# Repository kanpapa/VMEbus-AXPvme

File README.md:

# VMEbus-AXPvme
This repository contains documentation and sources for running DEC AXPvme 230

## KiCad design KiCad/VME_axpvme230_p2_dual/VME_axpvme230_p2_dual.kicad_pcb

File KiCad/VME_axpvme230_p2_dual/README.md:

# VME_axpvme230_p2_dual

DEC AXPvme 230 moduleをVMEラックに実装するためのAXPvme Dual Slot Breakout moduleです。

## Breakout boardの設計方針

* VMEラックにおいてAXPvme 230 moduleに確実に電源を供給することを目標にします。
* SCSIやその他の信号についてはコネクタに引き出すだけにします。
* 電源ラインは4層基板にすることで他の信号から電源ラインを分離します。

## KiCadデータ

KiCADで設計からガーバーデータの作成を行いました。

* [回路図](./VME_axpvme230_p2_dual_sch.pdf)
* [BOM](./VME_axpvme230_p2_dual.csv)
* [Garber](./gerber/)

## Dual Slot Breakout boardのイメージ図

## Disclaimer
The contents of this repository are the result of personal research and are provided "as is" without any warranty.

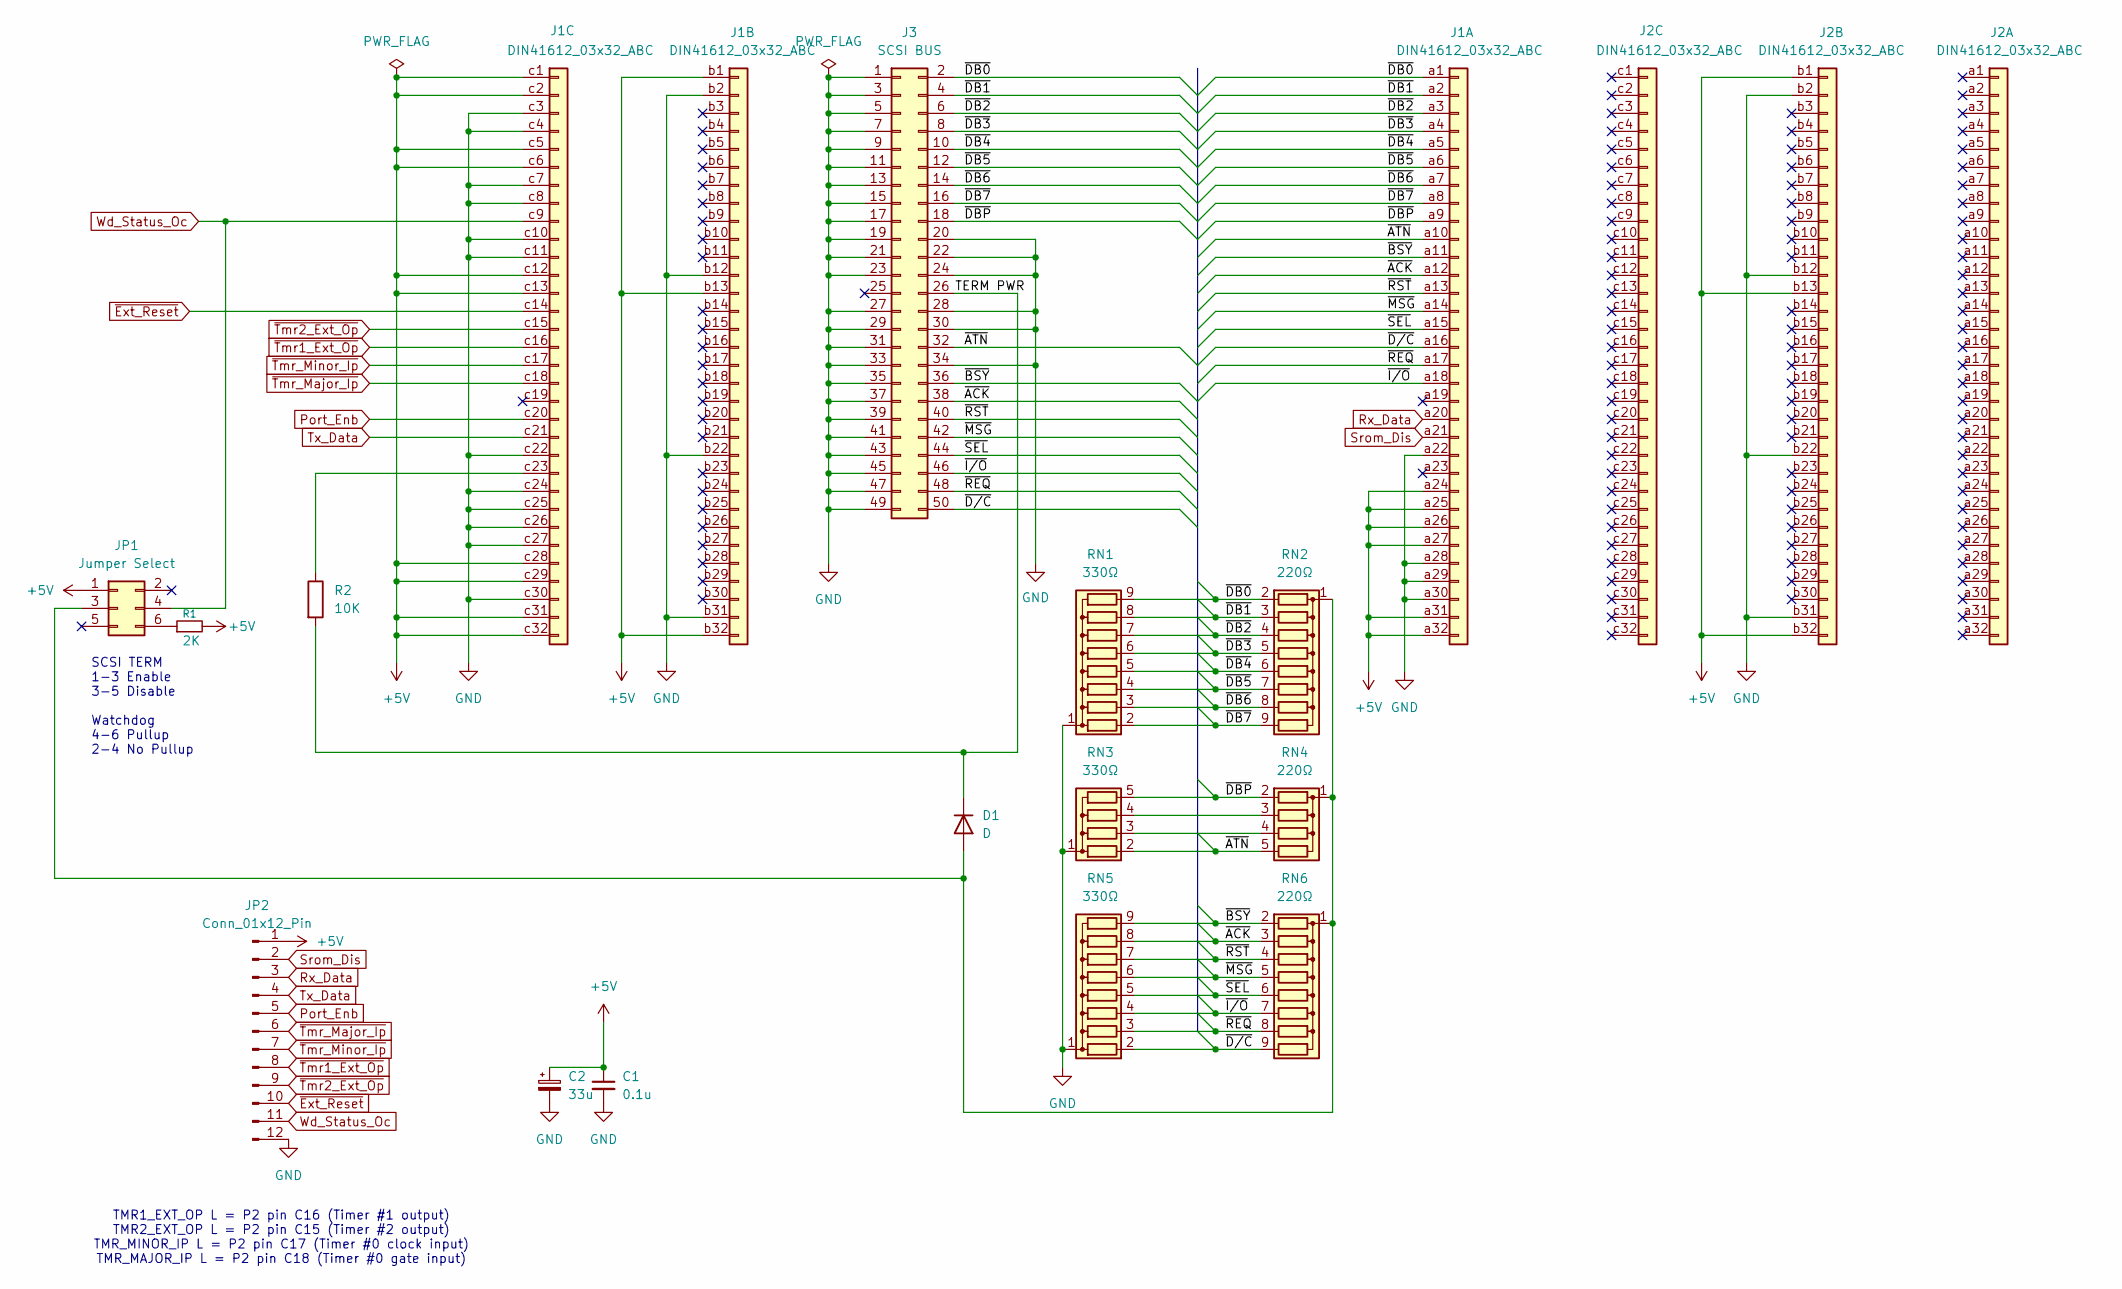
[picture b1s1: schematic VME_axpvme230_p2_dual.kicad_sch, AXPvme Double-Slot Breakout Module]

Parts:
C1: 0.1u; C_Disc_D3.4mm_W2.1mm_P2.50mm
C2: 33u; C_Radial_D4.0mm_H5.0mm_P1.50mm
D1: D; D_A-405_P7.62mm_Horizontal
J1, J2: DIN41612_03x32_ABC; DIN41612_C_3x32_Female_Vertical_THT
J3: SCSI BUS; IDC-Header_2x25_P2.54mm_Vertical
JP1: Jumper Select; PinHeader_2x03_P2.54mm_Vertical
JP2: Conn_01x12_Pin; PinHeader_1x12_P2.54mm_Vertical
R1: 2K; R_Axial_DIN0207_L6.3mm_D2.5mm_P7.62mm_Horizontal
R2: 10K; R_Axial_DIN0207_L6.3mm_D2.5mm_P7.62mm_Horizontal
RN1, RN5: 330Ω; R_Array_SIP9
RN2, RN6: 220Ω; R_Array_SIP9
RN3: 330Ω; R_Array_SIP5
RN4: 220Ω; R_Array_SIP5

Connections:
+5V: C1.1, C2.1, J1.a24, J1.a25, J1.a26, J1.a27, J1.a31, J1.a32, J1.b1, J1.b13, J1.b32, J1.c1, J1.c2, J1.c5, J1.c6, J1.c12, J1.c13, J1.c28, J1.c29, J1.c31, J1.c32, J2.b1, J2.b13, J2.b32, JP1.1, JP2.1, R1.2
/TERM PWR: D1.1 (K), J3.26, R2.2
/~ACK: J1.a12, J3.38, RN5.8 (R7), RN6.3 (R2)
/~ATN: J1.a10, J3.32, RN3.2 (R1), RN4.5 (R4)
/~BSY: J1.a11, J3.36, RN5.9 (R8), RN6.2 (R1)
/~DB0: J1.a1, J3.2, RN1.9 (R8), RN2.2 (R1)
/~DB1: J1.a2, J3.4, RN1.8 (R7), RN2.3 (R2)
/~DB2: J1.a3, J3.6, RN1.7 (R6), RN2.4 (R3)
/~DB3: J1.a4, J3.8, RN1.6 (R5), RN2.5 (R4)
/~DB4: J1.a5, J3.10, RN1.5 (R4), RN2.6 (R5)
/~DB5: J1.a6, J3.12, RN1.4 (R3), RN2.7 (R6)
/~DB6: J1.a7, J3.14, RN1.3 (R2), RN2.8 (R7)
/~DB7: J1.a8, J3.16, RN1.2 (R1), RN2.9 (R8)
/~DBP: J1.a9, J3.18, RN3.5 (R4), RN4.2 (R1)
/~D/C: J1.a16, J3.50, RN5.2 (R1), RN6.9 (R8)
/~I/O: J1.a18, J3.46, RN5.4 (R3), RN6.7 (R6)
/~MSG: J1.a14, J3.42, RN5.6 (R5), RN6.5 (R4)
/~REQ: J1.a17, J3.48, RN5.3 (R2), RN6.8 (R7)
/~RST: J1.a13, J3.40, RN5.7 (R6), RN6.4 (R3)
/~SEL: J1.a15, J3.44, RN5.5 (R4), RN6.6 (R5)
GND: C1.2, C2.2, J1.a22, J1.a28, J1.a29, J1.a30, J1.b2, J1.b12, J1.b22, J1.b31, J1.c3, J1.c4, J1.c7, J1.c8, J1.c10, J1.c11, J1.c22, J1.c24, J1.c25, J1.c26, J1.c27, J1.c30, J2.b2, J2.b12, J2.b22, J2.b31, J3.1, J3.3, J3.5, J3.7, J3.9, J3.11, J3.13, J3.15, J3.17, J3.19, J3.20, J3.21, J3.22, J3.23, J3.24, J3.27, J3.28, J3.29, J3.30, J3.31, J3.33, J3.34, J3.35, J3.37, J3.39, J3.41, J3.43, J3.45, J3.47, J3.49, JP2.12, RN1.1 (common), RN3.1 (common), RN5.1 (common)
unnamed: D1.2 (A), JP1.3, RN2.1 (common), RN4.1 (common), RN6.1 (common)
unnamed: J1.c23, R2.1
unnamed: JP1.6, R1.1
unnamed: RN3.3 (R2), RN4.4 (R3)
unnamed: RN3.4 (R3), RN4.3 (R2)
Port_Enb: J1.c20, JP2.5
Rx_Data: J1.a20, JP2.3
Srom_Dis: J1.a21, JP2.2
Tx_Data: J1.c21, JP2.4
Wd_Status_Oc: J1.c9, JP1.4, JP2.11
~Ext_Reset: J1.c14, JP2.10
~Tmr1_Ext_Op: J1.c16, JP2.8
~Tmr2_Ext_Op: J1.c15, JP2.9
~Tmr_Major_Ip: J1.c18, JP2.6
~Tmr_Minor_Ip: J1.c17, JP2.7

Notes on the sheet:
TMR1_EXT_OP L = P2 pin C16 (Timer #1 output) TMR2_EXT_OP L = P2 pin C15 (Timer #2 output) TMR_MINOR_IP L = P2 pin C17 (Timer #0 clock input) TMR_MAJOR_IP L = P2 pin C18 (Timer #0 gate input)
SCSI TERM 1-3 Enable 3-5 Disable Watchdog 4-6 Pullup 2-4 No Pullup

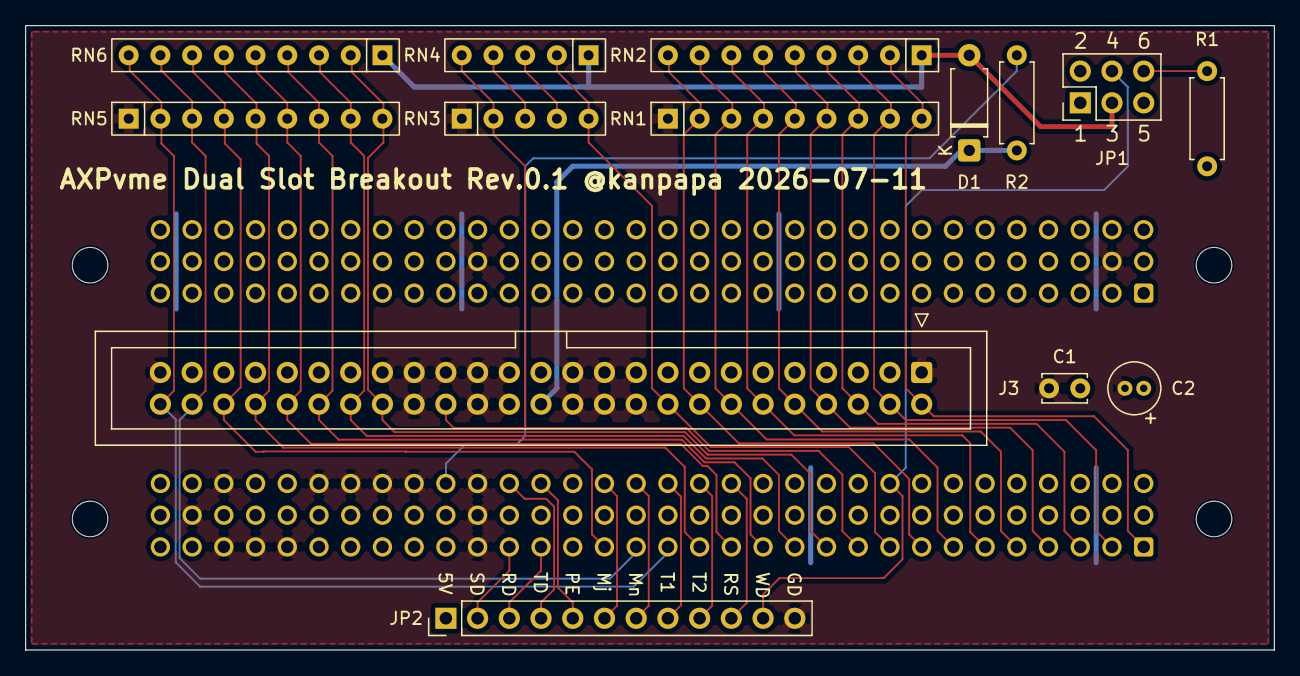
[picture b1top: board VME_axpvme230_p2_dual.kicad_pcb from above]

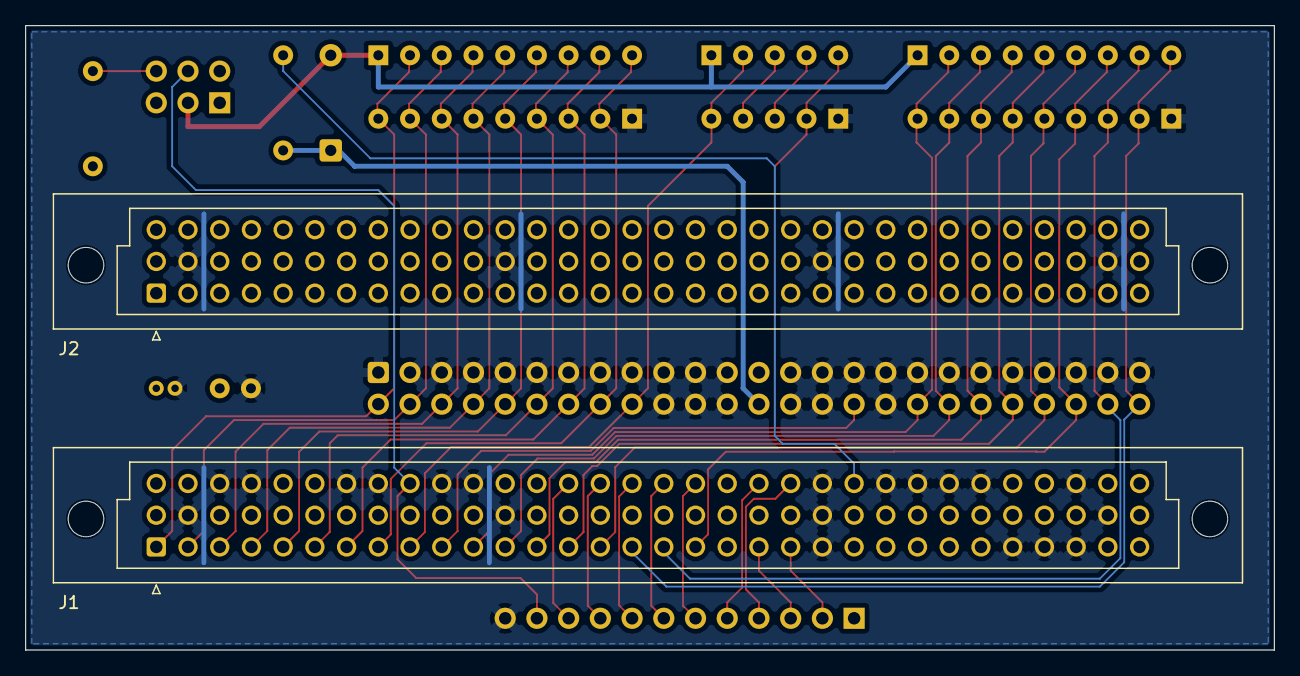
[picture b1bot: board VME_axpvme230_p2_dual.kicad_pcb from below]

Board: 4 copper layers, 100.0 x 50.0 mm, 16 parts (2 on the bottom side), 36 nets.

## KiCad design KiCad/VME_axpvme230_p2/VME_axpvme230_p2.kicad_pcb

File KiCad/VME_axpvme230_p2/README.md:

# VMEbus-axpvme230_p2

AXPvme 230 moduleを動作させるためには専用のAXPvme Breakout module (54-22621-01)が必要です。  
ドキュメントを参考にして簡易的なAXPvme Breakout boardを製作します。

## Breakout boardの設計方針

* AXPvme 230 moduleに確実に電源を供給することを目標にします。
* 試作の段階なので、VMEラックへの取り付けは行わず机上で確認できるようにシンプルなものにします。
* SCSIやその他の信号についてはコネクタに引き出すだけにします。
* 電源ラインは4層基板にすることで他の信号から電源ラインを分離します。
* [製作済のP1ブレイクアウトボード](https://github.com/kanpapa/VMEbus/tree/main/VME_power)と同じサイズにします。

## KiCadデータ

KiCADで設計からガーバーデータの作成を行いました。

* [回路図](./VME_axpvme230_p2_sch.pdf)
* [BOM](./VME_axpvme230_p2.csv)

## Breakout boardのイメージ図

## Disclaimer
The contents of this repository are the result of personal research and are provided "as is" without any warranty.

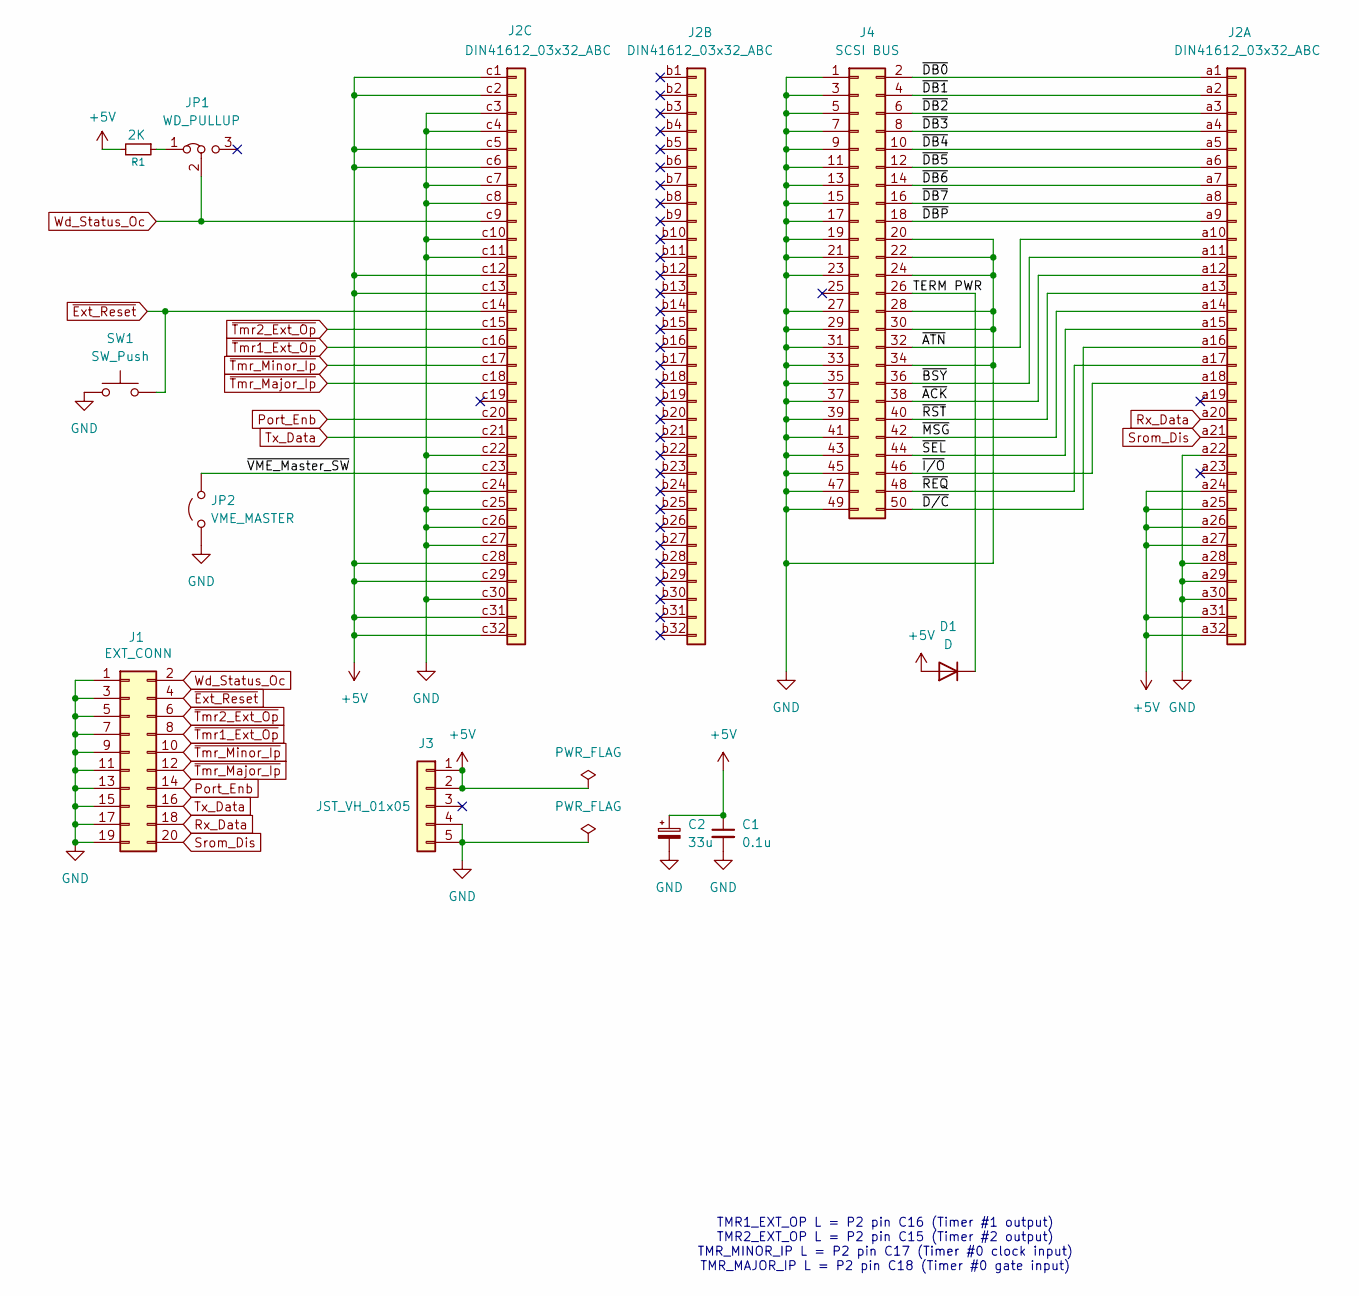
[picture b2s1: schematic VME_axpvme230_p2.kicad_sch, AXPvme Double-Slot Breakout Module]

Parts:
C1: 0.1u; C_Disc_D3.4mm_W2.1mm_P2.50mm
C2: 33u; C_Radial_D4.0mm_H5.0mm_P1.50mm
D1: D; D_A-405_P10.16mm_Horizontal
J1: EXT_CONN; PinHeader_2x10_P2.54mm_Vertical
J2: DIN41612_03x32_ABC; DIN41612_C_3x32_Male_Horizontal_THT
J3: JST_VH_01x05; JST_VH_B5P-VH_1x05_P3.96mm_Vertical
J4: SCSI BUS; IDC-Header_2x25_P2.54mm_Vertical
JP1: WD_PULLUP; PinHeader_1x03_P2.54mm_Vertical
JP2: VME_MASTER; PinHeader_1x02_P2.54mm_Vertical
R1: 2K; R_Axial_DIN0207_L6.3mm_D2.5mm_P10.16mm_Horizontal
SW1: SW_Push; SW_PUSH_6mm

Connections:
+5V: C1.1, C2.1, D1.2 (A), J2.a24, J2.a25, J2.a26, J2.a27, J2.a31, J2.a32, J2.c1, J2.c2, J2.c5, J2.c6, J2.c12, J2.c13, J2.c28, J2.c29, J2.c31, J2.c32, J3.1, J3.2, R1.2
/TERM PWR: D1.1 (K), J4.26
/~ACK: J2.a12, J4.38
/~ATN: J2.a10, J4.32
/~BSY: J2.a11, J4.36
/~DB0: J2.a1, J4.2
/~DB1: J2.a2, J4.4
/~DB2: J2.a3, J4.6
/~DB3: J2.a4, J4.8
/~DB4: J2.a5, J4.10
/~DB5: J2.a6, J4.12
/~DB6: J2.a7, J4.14
/~DB7: J2.a8, J4.16
/~DBP: J2.a9, J4.18
/~D/C: J2.a16, J4.50
/~I/O: J2.a18, J4.46
/~MSG: J2.a14, J4.42
/~REQ: J2.a17, J4.48
/~RST: J2.a13, J4.40
/~SEL: J2.a15, J4.44
/~VME_Master_SW: J2.c23, JP2.2 (B)
GND: C1.2, C2.2, J1.1, J1.3, J1.5, J1.7, J1.9, J1.11, J1.13, J1.15, J1.17, J1.19, J2.a22, J2.a28, J2.a29, J2.a30, J2.c3, J2.c4, J2.c7, J2.c8, J2.c10, J2.c11, J2.c22, J2.c24, J2.c25, J2.c26, J2.c27, J2.c30, J3.4, J3.5, J4.1, J4.3, J4.5, J4.7, J4.9, J4.11, J4.13, J4.15, J4.17, J4.19, J4.20, J4.21, J4.22, J4.23, J4.24, J4.27, J4.28, J4.29, J4.30, J4.31, J4.33, J4.34, J4.35, J4.37, J4.39, J4.41, J4.43, J4.45, J4.47, J4.49, JP2.1 (A), SW1.1
unnamed: JP1.1 (A), R1.1
Port_Enb: J1.14, J2.c20
Rx_Data: J1.18, J2.a20
Srom_Dis: J1.20, J2.a21
Tx_Data: J1.16, J2.c21
Wd_Status_Oc: J1.2, J2.c9, JP1.2 (C)
~Ext_Reset: J1.4, J2.c14, SW1.2
~Tmr1_Ext_Op: J1.8, J2.c16
~Tmr2_Ext_Op: J1.6, J2.c15
~Tmr_Major_Ip: J1.12, J2.c18
~Tmr_Minor_Ip: J1.10, J2.c17

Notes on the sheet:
TMR1_EXT_OP L = P2 pin C16 (Timer #1 output) TMR2_EXT_OP L = P2 pin C15 (Timer #2 output) TMR_MINOR_IP L = P2 pin C17 (Timer #0 clock input) TMR_MAJOR_IP L = P2 pin C18 (Timer #0 gate input)

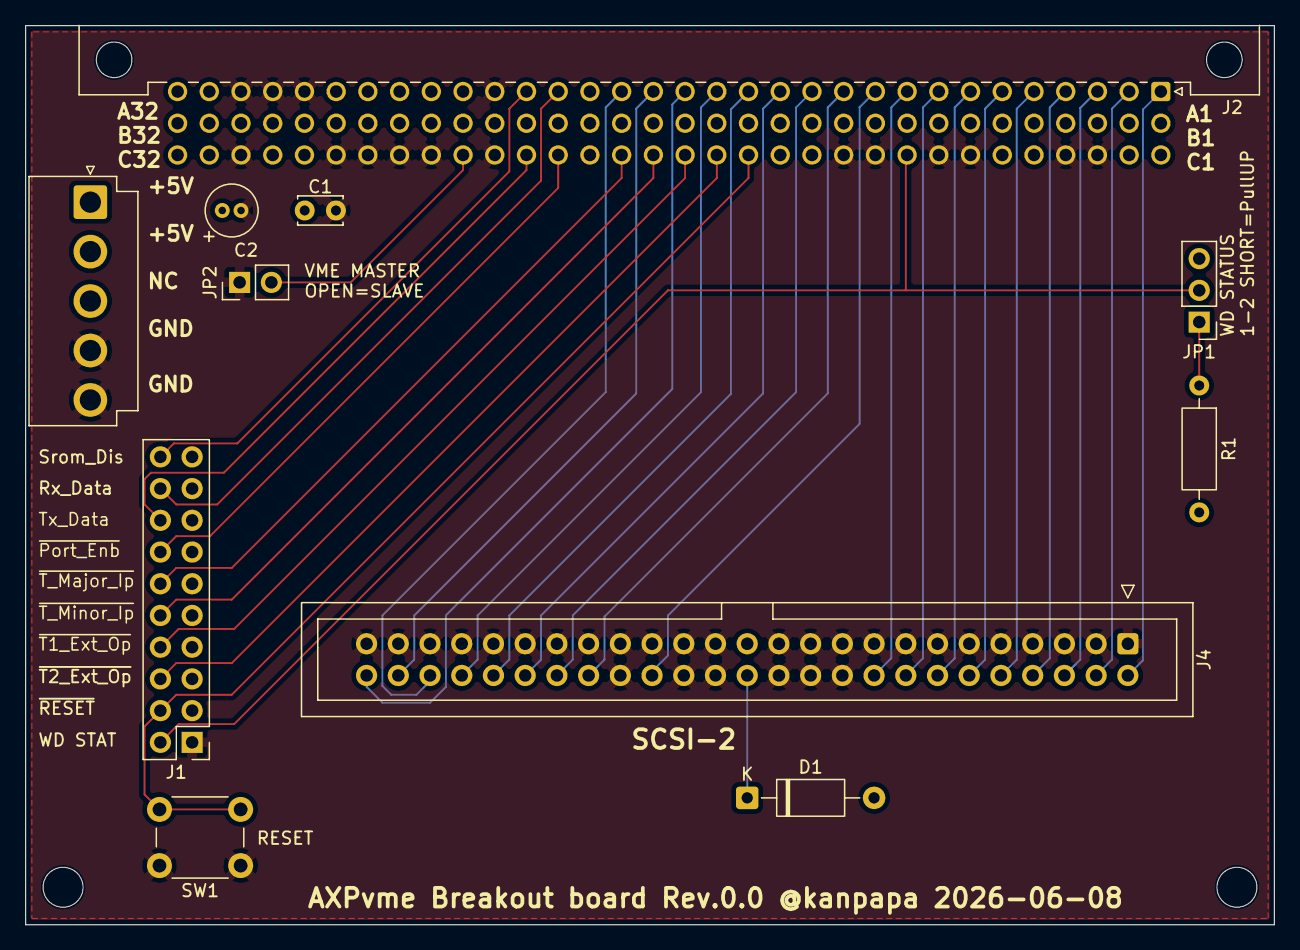
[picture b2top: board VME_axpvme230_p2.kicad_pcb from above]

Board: 4 copper layers, 100.0 x 72.0 mm, 13 parts (0 on the bottom side), 33 nets.

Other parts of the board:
MH1, MH2: MountingHole_3.2mm_M3

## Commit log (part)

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2026-06-13 1st commit
2026-06-13 CSVのカラム修正
2026-06-13 BOMで品番違いを修正
2026-06-14 BOMの修正
2026-06-14 Breakout boardのREADMEを追加
2026-06-14 回路図を差し替え
2026-06-14 ハイフンが違うコードだったので修正
2026-06-16 Added led_test
